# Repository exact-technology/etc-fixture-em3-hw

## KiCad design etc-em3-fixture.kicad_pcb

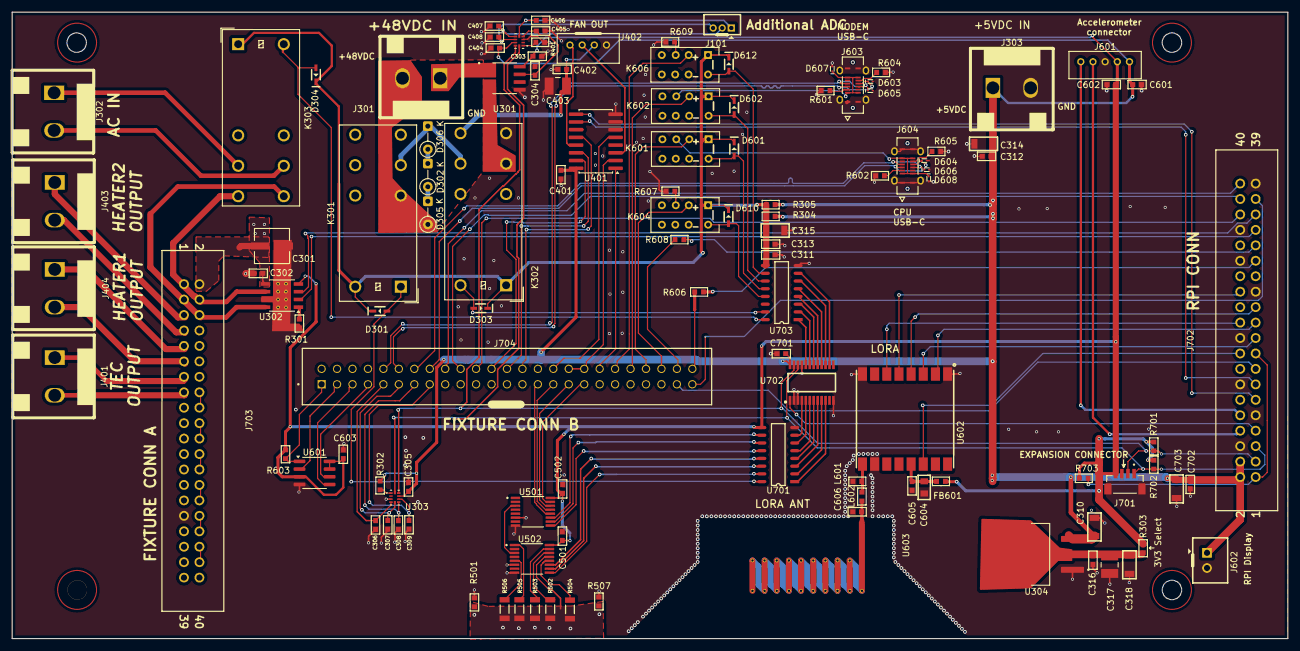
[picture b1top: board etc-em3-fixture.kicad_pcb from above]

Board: 2 copper layers, 209.8 x 103.0 mm, 118 parts (0 on the bottom side), 133 nets.

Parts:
C301: EEH-ZC1K470P; CAP_1K470P_PAN
C302, C303, C304, C305, C306, C307, C308, C309, C311, C312, C313, C316, C401, C402, C404, C405, C406, C407, C408, C501, C502, C601, C602, C603, C604, C606, C702: VALUE; CAP_0603
C310, C314, C315, C318, C703: VALUE; CAP_1206
C317, C403: VALUE; CAP_1210
C605: VALUE; CAP_0805
C701: CAP_0603
D301, D303, D304, D601, D602, D610, D612: VALUE; SOD323
D302, D305, D306: 1N5408; D_DO-35_SOD27_P3.81mm_Vertical_KathodeUp
D603, D604, D605, D606, D607, D608: ESD7951ST5G; SOD923
FB601: VALUE; RES_0603
J101: 15SH-A-03-TS
J301, J302, J303, J401, J403, J404: DME-03; B02P-VL
J402: SWR201-NRTN-S04-SA-WH; 4POS 2MM JSY
J601: SWR201-NRTN-S05-SA-WH; 5POS 2MM JST
J602: 1-00084; B2B-XH-A(LF)(SN)
J603, J604: *; MOLEX_2171820001
J701: 1-00837; JST_BM04B-SRSS-TB(LF)(SN)
J702, J703: 1-00777; TST-120-01-X-D
J704: 1-00785; TSS-125-01-T-D
K301, K302, K303: G2RL-2; Relay_DPDT_Omron_G2RL-2
K601, K602, K604, K606: 1-00784; KEMET_UA2
L601, L602: VALUE; RES_0603
R301, R302, R303, R304, R305, R401, R501, R507, R601, R602, R603, R604, R605, R606, R607, R608, R609, R702, R703: VALUE; RES_0603
R502, R503, R504, R505, R506: VALUE; RES_1206
R701: RES_0603
U301: TMCS1108; SOIC127P599X175-8N
U302: *; Texas_HSOP-8-1EP_3.9x4.9mm_P1.27mm_ThermalVias
U303, U402: 1-00780; IC_ADS1115IRUGR
U304: LM1085-3.3; TO254P1524X483-4N
U401: *; SOIC-16W_5.3x10.2mm_P1.27mm
U501, U502: XS3A4051PWJ; 16-TSSOP
U601: M95256-WMN6P; SOIC-8_3.9x4.9mm_P1.27mm
U602: Lora1276-C1
U603: PCB Antenna 868MHz - 925MHz; DN038
U701, U703: ULN2003ADRG3; 16-SOIC
U702: PCA9675PW,118; SOP65P640X110-24N

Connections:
+3V3: C303.1, C501.1, C502.1, C602.1, C603.1, FB601.2, J601.4, J701.4, R303.1, R603.1, R701.1, R702.1, R703.1, U301.8 (VS), U302.4 (VREF), U501.16 (VCC), U502.16 (VCC), U601.3 (~W), U601.7 (~HOLD), U601.8 (VCC), U701.9 (COM)
+48V: C301.1, C302.2, C402.2, C403.1, J402.3, J703.2, K302.24, U302.5 (VM)
/Connectors/+48_RLY: D303.2 (K), K302.A2, U703.15 (2C)
/Connectors/BROWN_OUT: D301.2 (K), K301.A1, U701.16 (1C)
/Connectors/CPU_RLY: D601.2 (K), K601.8, U703.12 (5C)
/Connectors/FAN_SEL1: J702.13, U401.10 (A)
/Connectors/FAN_SEL2: J702.11, U401.9 (B)
/Connectors/LED1: J702.29, R606.1
/Connectors/LED2: J702.31, R608.1
/Connectors/LORA_IO: J702.18, U602.14 (DIO0)
/Connectors/LORA_RESET: J702.22, U602.6 (NRESET)
/Connectors/Modem_RLY: D602.2 (K), K602.8, U703.11 (6C)
/Connectors/RESET_N: J702.40, J704.18
/Connectors/RLY_BTN1: D610.2 (K), K604.8, U703.13 (4C)
/Connectors/RLY_BTN2: D612.2 (K), K606.8, U703.10 (7C)
/Connectors/RPI_INT: J702.7, U702.1 (~INT)
/Connectors/RPI_RX: J601.1, J702.10
/Connectors/RPI_SCL1: J701.1, J702.5, R702.2, U303.10 (SCL), U402.10 (SCL), U702.22 (SCL)
/Connectors/RPI_SDA1: J701.2, J702.3, R701.2, U303.9 (SDA), U402.9 (SDA), U702.23 (SDA)
/Connectors/RPI_TX: J601.2, J702.8
/Connectors/RP_ANALOG_PROBE_SEL0: U501.11 (S1), U701.10 (7C)
/Connectors/RP_ANALOG_PROBE_SEL1: U501.10 (S2), U701.11 (6C)
/Connectors/RP_ANALOG_PROBE_SEL2: U501.9 (S3), U701.12 (5C)
/Connectors/RP_ANALOG_RES_SEL0: U502.11 (S1), U701.13 (4C)
/Connectors/RP_ANALOG_RES_SEL1: U502.10 (S2), U701.14 (3C)
/Connectors/RP_ANALOG_RES_SEL2: U502.9 (S3), U701.15 (2C)
/Connectors/RP_PWM1: J702.35, U302.3 (IN1)
/Connectors/RP_PWM2: J702.33, U302.2 (IN2)
/Connectors/SPI0_LORA_CS: J702.26, U602.5 (NSS)
/Connectors/SPI0_MISO: J702.21, U602.2 (MISO)
/Connectors/SPI0_MOSI: J702.19, U602.3 (MOSI)
/Connectors/SPI0_SCK: J702.23, U602.4 (SCK)
/Connectors/TP1: J702.15, J704.47
/Connectors/TP13: J703.3, J703.6, K303.24, U302.8 (OUT2)
/Connectors/TP14: J703.1, J703.4, K303.14, U302.6 (OUT1)
/Connectors/TP21: J704.44, K601.2
/Connectors/TP24: J704.42, K602.2
/Connectors/TP25: C307.2, J704.11, U303.5 (AIN1)
/Connectors/TP30: C309.2, J704.15, U303.7 (AIN3)
/Connectors/TP32: C306.2, J704.9, U303.4 (AIN0)
/Connectors/TP33: C308.2, J704.13, U303.6 (AIN2)
/Connectors/TP34: J403.2, J703.7
/Connectors/TP35: J404.1, J703.9
/Connectors/TP36: J403.1, J703.5
/Connectors/TP37: J404.2, J703.11
/Connectors/TP48: J703.32, J703.34
/Connectors/TP50: J704.31, U501.13 (Y0)
/Connectors/TP51: J703.36, J703.38
/Connectors/TP52: J703.20, J703.22
/Connectors/TP53: J704.35, U501.15 (Y2)
/Connectors/TP54: J704.29, U501.12 (Y3)
/Connectors/TP55: J704.33, U501.14 (Y1)
/Connectors/TP56: J704.28, U401.12 (X0)
/Connectors/TP57: J704.38, U401.1 (Y0)
/Connectors/TP58: J704.26, U401.14 (X1)
/Connectors/TP59: J704.32, U401.5 (Y1)
/Connectors/TP60: J704.24, U401.15 (X2)
/Connectors/TP61: J704.34, J704.36, U401.2 (Y2)
/Connectors/TP67: J703.16, J703.18
/Connectors/TP68: J703.28, J703.30
/Connectors/TP69: J703.24, J703.26
/Connectors/TP73: J702.37, J704.49
/Connectors/TP74: J704.40, K606.2
/Connectors/TP75: J704.48, R608.2
/Connectors/TP76: J704.46, K604.2
/Connectors/TP77: J704.50, R606.2
/Connectors/TP78: J702.36, J704.22
/Connectors/TP79: J702.38, J704.20
/Connectors/TP92: J704.3, U601.2 (Q)
/Connectors/TP93: J704.1, R603.2, U601.1 (~S)
/Connectors/TP94: J704.7, U601.6 (C)
/Connectors/TP95: J704.5, U601.5 (D)
/Connectors/TP96: J401.1, J703.13
/Connectors/TP97: J401.2, J703.15
/Connectors/VAC_RLY: D304.2 (K), K303.A2, U703.16 (1C)
/FAN-TEC-HEATER/PWM: J402.1, U401.13 (X)
/FAN-TEC-HEATER/SENS_TEC: C304.2, C405.2, U301.7 (VOUT), U402.4 (AIN0)
/FAN-TEC-HEATER/TACH: J402.2, U401.3 (Y)
/POWER/VAC(L): J302.1, K303.11
/POWER/VAC(N): J302.2, K303.21
/Peripheral test/CPU_N: D604.2 (K), J604.A6 (DP1), J604.B6 (DP2), J704.16
/Peripheral test/CPU_P: D606.2 (K), J604.A7 (DN1), J604.B7 (DN2), J704.14
/Peripheral test/L_N: D603.2 (K), J603.A6 (DP1), J603.B6 (DP2), J704.12
/Peripheral test/L_P: D605.2 (K), J603.A7 (DN1), J603.B7 (DN2), J704.10
AGND: R501.1, R502.1, R503.1, R504.1, R505.1, R506.1, R507.1, U502.13 (Y0)
GND: C301.2, C302.1, C303.2, C304.1, C305.2, C306.1, C307.1, C308.1, C309.1, C310.2, C311.2, C312.1, C313.1, C314.1, C315.2, C316.1, C317.2, C318.1, C401.2, C402.1, C403.2, C404.2, C405.1, C406.1, C407.1, C408.1, C501.2, C502.2, C601.2, C602.2, C603.2, C604.2, C605.1, C606.1, C701.2, C702.2, C703.1, D603.1 (A), D604.1 (A), D605.1 (A), D606.1 (A), D607.1 (A), D608.1 (A), J303.2, J402.4, J601.3, J602.2, J603.A1 (GND), J603.A12 (GND), J603.B1 (GND), J603.B12 (GND), J603.SH1 (SHIELD), J603.SH2 (SHIELD), J603.SH3 (SHIELD), J603.SH4 (SHIELD), J604.A1 (GND), J604.A12 (GND), J604.B1 (GND), J604.B12 (GND), J604.SH1 (SHIELD), J604.SH2 (SHIELD), J604.SH3 (SHIELD), J604.SH4 (SHIELD), J701.3, J701.S1, J701.S2, J702.6, J702.9, J702.14, J702.20, J702.25, J702.30, J702.34, J702.39, J703.31, K302.14, L601.1, R301.1, R401.2, R501.2, R507.2, R601.1, R602.1, R604.2, R605.2, R607.1, R609.1, U301.5 (GND), U302.7 (GND), U302.9 (EPAD), U303.3 (GND), U304.1 (GND), U401.6 (INH), U401.7 (VEE), U401.8 (VSS), U402.3 (GND), U501.6 (~E), U501.8 (GND), U502.6 (~E), U502.8 (GND), U601.4 (VSS), U602.1 (GND), U602.8 (GND), U602.10 (GND), U701.8 (E), U702.2 (AD1), U702.3 (AD2), U702.12 (VSS), U702.21 (AD0), U703.8 (E)
unnamed: C316.2, C317.1, C318.2, R303.2, U304.2 (OUT), U304.4 (OUT)
unnamed: D302.2 (A), D305.1 (K)
unnamed: D302.1 (K), D306.2 (A)
unnamed: D305.2 (A), J301.2, K301.12
unnamed: D306.1 (K), K301.11, K302.21
unnamed: D607.2 (K), J603.A4 (VBUS), J603.A9 (VBUS), J603.B4 (VBUS), J603.B9 (VBUS), K602.3
unnamed: D608.2 (K), J604.A4 (VBUS), J604.A9 (VBUS), J604.B4 (VBUS), J604.B9 (VBUS), K601.3
unnamed: J301.1, U301.1 (IN+), U301.2 (IN+)
unnamed: J603.A5 (CC1), R601.2
unnamed: J603.B5 (CC2), R604.1
unnamed: J604.A5 (CC1), R602.2
unnamed: J604.B5 (CC2), R605.1
unnamed: J702.1, J702.17, R703.2
unnamed: K302.11, U301.3 (IN-), U301.4 (IN-)
unnamed: K604.3, R607.2
unnamed: K606.3, R609.2
unnamed: R301.2, U302.1 (IPROPI)
unnamed: R302.2, U303.1 (ADDR)
unnamed: R401.1, U402.1 (ADDR)
unnamed: C406.2, J101.1, U402.5 (AIN1)
unnamed: C407.2, J101.2, U402.6 (AIN2)
unnamed: C408.2, J101.3, U402.7 (AIN3)
unnamed: U501.3 (Z), U502.3 (Z)
unnamed: R502.2, U502.14 (Y1)
unnamed: R503.2, U502.15 (Y2)
unnamed: R504.2, U502.12 (Y3)
unnamed: R505.2, U502.1 (Y4)
unnamed: R506.2, U502.5 (Y5)
unnamed: L601.2, L602.1, U602.9 (ANT)
unnamed: C606.2, L602.2
unnamed: U701.1 (1B), U702.10 (P06)
unnamed: U701.2 (2B), U702.9 (P05)
unnamed: U701.3 (3B), U702.8 (P04)
unnamed: U701.4 (4B), U702.7 (P03)
unnamed: U701.5 (5B), U702.6 (P02)
unnamed: U701.6 (6B), U702.5 (P01)
unnamed: U701.7 (7B), U702.4 (P00)
unnamed: U702.14 (P11), U703.7 (7B)
unnamed: U702.15 (P12), U703.6 (6B)
unnamed: U702.16 (P13), U703.5 (5B)
unnamed: U702.17 (P14), U703.4 (4B)
unnamed: U702.18 (P15), U703.3 (3B)
unnamed: U702.19 (P16), U703.2 (2B)
unnamed: U702.20 (P17), U703.1 (1B)
VCC: C305.1, C310.1, C312.2, C314.2, C401.1, C404.1, C601.1, C701.1, C702.1, C703.2, J303.1, J601.5, J602.1, J702.2, J702.4, R302.1, R304.1, R305.1, U303.8 (VDD), U304.3 (VIN), U401.16 (VDD), U402.8 (VDD), U702.24 (VDD)
VCC_LORA: C604.1, C605.2, FB601.1, U602.13 (VCC)
VCC_RLY: C311.1, C313.2, C315.1, D301.1 (A), D303.1 (A), D304.1 (A), D601.1 (A), D602.1 (A), D610.1 (A), D612.1 (A), K301.A2, K302.A1, K303.A1, K601.1, K602.1, K604.1, K606.1, R304.2, R305.2, U703.9 (COM)

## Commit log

2025-07-22 latest rev
2025-07-23 V0.1 for review
2025-08-18 Commit after Review
2025-08-19 Review
2025-08-21 Revised PCBA
